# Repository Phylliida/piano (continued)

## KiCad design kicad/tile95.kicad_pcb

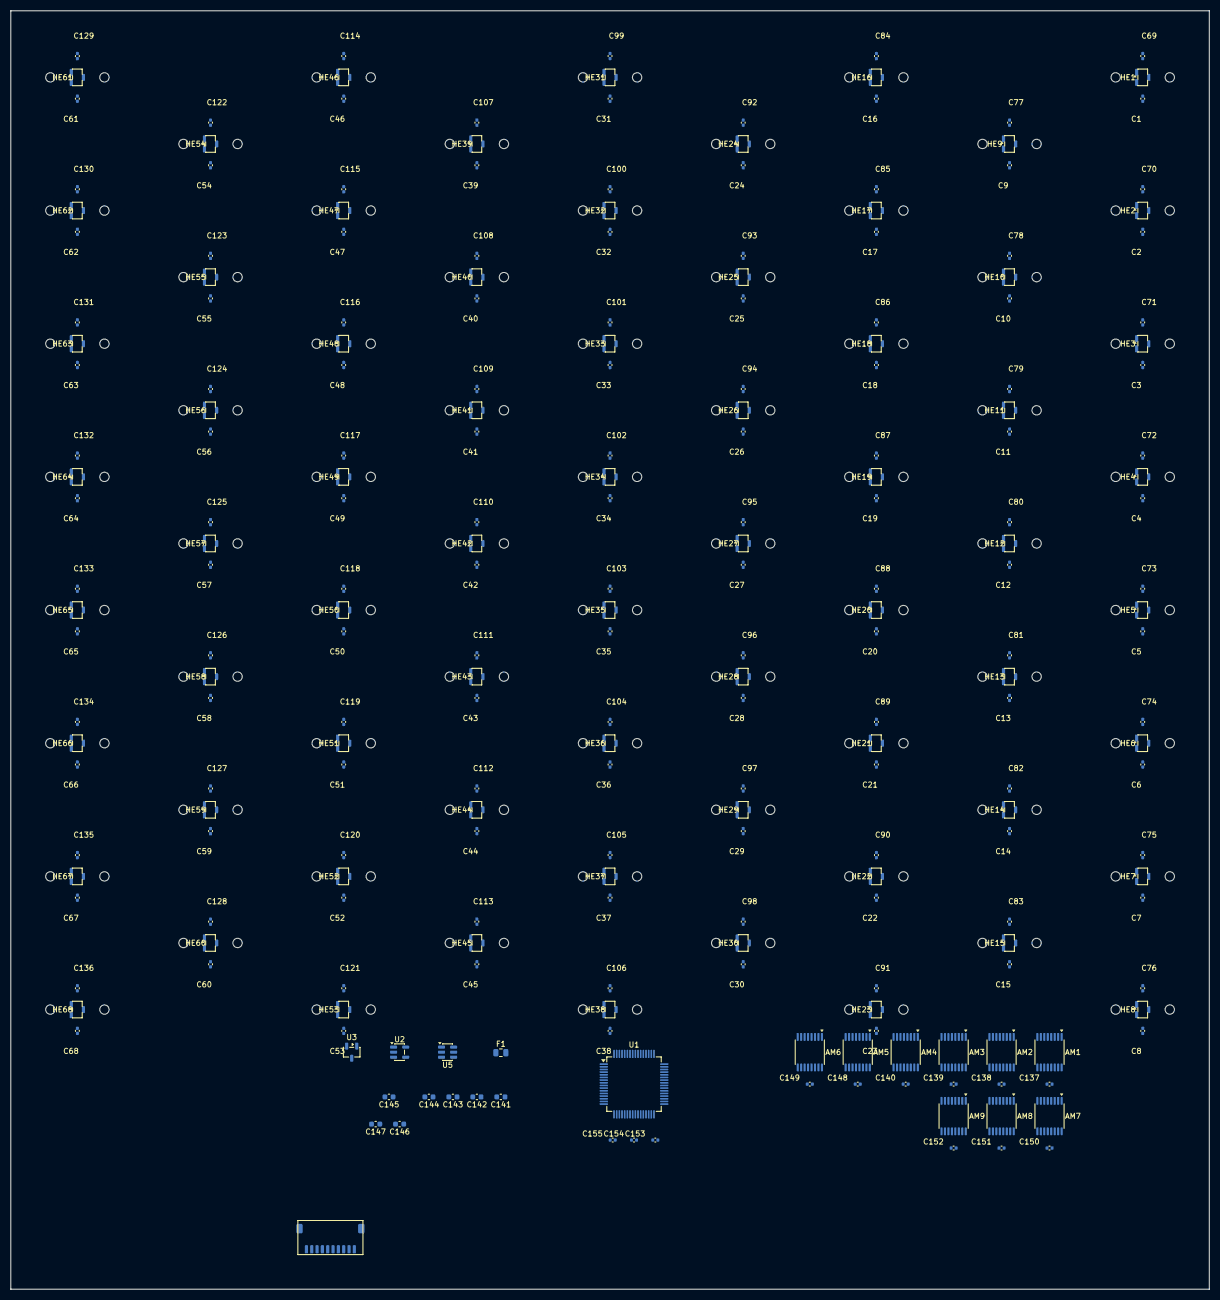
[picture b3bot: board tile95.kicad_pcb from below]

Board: 2 copper layers, 225.0 x 240.0 mm, 306 parts (238 on the bottom side), 89 nets, no tracks yet.

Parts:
AM1, AM2, AM3, AM4, AM5, AM6, AM7, AM8, AM9: SN74LV4051A; TSSOP-16_4.4x5mm_P0.65mm
C1, C2, C3, C4, C5, C6, C7, C8, C9, C10, C11, C12, C13, C14, C15, C16, C17, C18, C19, C20, C21, C22, C23, C24, C25, C26, C27, C28, C29, C30, C31, C32, C33, C34, C35, C36, C37, C38, C39, C40, C41, C42, C43, C44, C45, C46, C47, C48, C49, C50, C51, C52, C53, C54, C55, C56, C57, C58, C59, C60, C61, C62, C63, C64, C65, C66, C67, C68: 4.7n; C_0402_1005Metric
C69, C70, C71, C72, C73, C74, C75, C76, C77, C78, C79, C80, C81, C82, C83, C84, C85, C86, C87, C88, C89, C90, C91, C92, C93, C94, C95, C96, C97, C98, C99, C100, C101, C102, C103, C104, C105, C106, C107, C108, C109, C110, C111, C112, C113, C114, C115, C116, C117, C118, C119, C120, C121, C122, C123, C124, C125, C126, C127, C128, C129, C130, C131, C132, C133, C134, C135, C136, C137, C138, C139, C140, C148, C149, C150, C151, C152, C153, C154, C155: 100n; C_0402_1005Metric
C141, C142, C143, C144, C146: 2.2u; C_0603_1608Metric
C145: 10u; C_0603_1608Metric
C147: 1u; C_0603_1608Metric
F1: BSMD0805-050-24V; Fuse_0805_2012Metric
HE1, HE2, HE3, HE4, HE5, HE6, HE7, HE8, HE9, HE10, HE11, HE12, HE13, HE14, HE15, HE16, HE17, HE18, HE19, HE20, HE21, HE22, HE23, HE24, HE25, HE26, HE27, HE28, HE29, HE30, HE31, HE32, HE33, HE34, HE35, HE36, HE37, HE38, HE39, HE40, HE41, HE42, HE43, HE44, HE45, HE46, HE47, HE48, HE49, HE50, HE51, HE52, HE53, HE54, HE55, HE56, HE57, HE58, HE59, HE60, HE61, HE62, HE63, HE64, HE65, HE66, HE67, HE68: GH39FKSW; SOT-23-3
J1: SM10B-SRSS-TB; JST_SH_SM10B-SRSS-TB_1x10-1MP_P1.00mm_Horizontal
SW1, SW2, SW3, SW4, SW5, SW6, SW7, SW8, SW9, SW10, SW11, SW12, SW13, SW14, SW15, SW16, SW17, SW18, SW19, SW20, SW21, SW22, SW23, SW24, SW25, SW26, SW27, SW28, SW29, SW30, SW31, SW32, SW33, SW34, SW35, SW36, SW37, SW38, SW39, SW40, SW41, SW42, SW43, SW44, SW45, SW46, SW47, SW48, SW49, SW50, SW51, SW52, SW53, SW54, SW55, SW56, SW57, SW58, SW59, SW60, SW61, SW62, SW63, SW64, SW65, SW66, SW67, SW68: MX-1U
U1: AT32F405RCT7; LQFP-64_10x10mm_P0.5mm
U2: TLV75733PDBV; SOT-23-5
U3: XC6206P332MR-G; SOT-23-3
U5: USBLC6-2SC6; SOT-23-6

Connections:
5V: C141.1, C142.1, C143.1, C144.1, F1.2, U2.1 (IN), U2.3 (EN), U3.3 (GND), U5.5 (VBUS)
+3V3: C145.1, C153.1, C154.1, C155.1, U1.1 (VDD), U1.36 (VDD), U1.64 (VDD), U3.2 (OUT)
+3V3A: AM1.16 (VDD), AM2.16 (VDD), AM3.16 (VDD), AM4.16 (VDD), AM5.16 (VDD), AM6.16 (VDD), AM7.16 (VDD), AM8.16 (VDD), AM9.16 (VDD), C69.1, C70.1, C71.1, C72.1, C73.1, C74.1, C75.1, C76.1, C77.1, C78.1, C79.1, C80.1, C81.1, C82.1, C83.1, C84.1, C85.1, C86.1, C87.1, C88.1, C89.1, C90.1, C91.1, C92.1, C93.1, C94.1, C95.1, C96.1, C97.1, C98.1, C99.1, C100.1, C101.1, C102.1, C103.1, C104.1, C105.1, C106.1, C107.1, C108.1, C109.1, C110.1, C111.1, C112.1, C113.1, C114.1, C115.1, C116.1, C117.1, C118.1, C119.1, C120.1, C121.1, C122.1, C123.1, C124.1, C125.1, C126.1, C127.1, C128.1, C129.1, C130.1, C131.1, C132.1, C133.1, C134.1, C135.1, C136.1, C137.1, C138.1, C139.1, C140.1, C146.1, C147.1, C148.1, C149.1, C150.1, C151.1, C152.1, HE1.1 (VCC), HE2.1 (VCC), HE3.1 (VCC), HE4.1 (VCC), HE5.1 (VCC), HE6.1 (VCC), HE7.1 (VCC), HE8.1 (VCC), HE9.1 (VCC), HE10.1 (VCC), HE11.1 (VCC), HE12.1 (VCC), HE13.1 (VCC), HE14.1 (VCC), HE15.1 (VCC), HE16.1 (VCC), HE17.1 (VCC), HE18.1 (VCC), HE19.1 (VCC), HE20.1 (VCC), HE21.1 (VCC), HE22.1 (VCC), HE23.1 (VCC), HE24.1 (VCC), HE25.1 (VCC), HE26.1 (VCC), HE27.1 (VCC), HE28.1 (VCC), HE29.1 (VCC), HE30.1 (VCC), HE31.1 (VCC), HE32.1 (VCC), HE33.1 (VCC), HE34.1 (VCC), HE35.1 (VCC), HE36.1 (VCC), HE37.1 (VCC), HE38.1 (VCC), HE39.1 (VCC), HE40.1 (VCC), HE41.1 (VCC), HE42.1 (VCC), HE43.1 (VCC), HE44.1 (VCC), HE45.1 (VCC), HE46.1 (VCC), HE47.1 (VCC), HE48.1 (VCC), HE49.1 (VCC), HE50.1 (VCC), HE51.1 (VCC), HE52.1 (VCC), HE53.1 (VCC), HE54.1 (VCC), HE55.1 (VCC), HE56.1 (VCC), HE57.1 (VCC), HE58.1 (VCC), HE59.1 (VCC), HE60.1 (VCC), HE61.1 (VCC), HE62.1 (VCC), HE63.1 (VCC), HE64.1 (VCC), HE65.1 (VCC), HE66.1 (VCC), HE67.1 (VCC), HE68.1 (VCC), U1.13 (VDDA), U2.5 (OUT)
GND: AM1.6 (Inh), AM1.7 (VEE), AM1.8 (VSS), AM2.6 (Inh), AM2.7 (VEE), AM2.8 (VSS), AM3.6 (Inh), AM3.7 (VEE), AM3.8 (VSS), AM4.6 (Inh), AM4.7 (VEE), AM4.8 (VSS), AM5.6 (Inh), AM5.7 (VEE), AM5.8 (VSS), AM6.6 (Inh), AM6.7 (VEE), AM6.8 (VSS), AM7.6 (Inh), AM7.7 (VEE), AM7.8 (VSS), AM8.6 (Inh), AM8.7 (VEE), AM8.8 (VSS), AM9.6 (Inh), AM9.7 (VEE), AM9.8 (VSS), AM9.12 (X3), AM9.13 (X0), AM9.14 (X1), AM9.15 (X2), C1.2, C2.2, C3.2, C4.2, C5.2, C6.2, C7.2, C8.2, C9.2, C10.2, C11.2, C12.2, C13.2, C14.2, C15.2, C16.2, C17.2, C18.2, C19.2, C20.2, C21.2, C22.2, C23.2, C24.2, C25.2, C26.2, C27.2, C28.2, C29.2, C30.2, C31.2, C32.2, C33.2, C34.2, C35.2, C36.2, C37.2, C38.2, C39.2, C40.2, C41.2, C42.2, C43.2, C44.2, C45.2, C46.2, C47.2, C48.2, C49.2, C50.2, C51.2, C52.2, C53.2, C54.2, C55.2, C56.2, C57.2, C58.2, C59.2, C60.2, C61.2, C62.2, C63.2, C64.2, C65.2, C66.2, C67.2, C68.2, C69.2, C70.2, C71.2, C72.2, C73.2, C74.2, C75.2, C76.2, C77.2, C78.2, C79.2, C80.2, C81.2, C82.2, C83.2, C84.2, C85.2, C86.2, C87.2, C88.2, C89.2, C90.2, C91.2, C92.2, C93.2, C94.2, C95.2, C96.2, C97.2, C98.2, C99.2, C100.2, C101.2, C102.2, C103.2, C104.2, C105.2, C106.2, C107.2, C108.2, C109.2, C110.2, C111.2, C112.2, C113.2, C114.2, C115.2, C116.2, C117.2, C118.2, C119.2, C120.2, C121.2, C122.2, C123.2, C124.2, C125.2, C126.2, C127.2, C128.2, C129.2, C130.2, C131.2, C132.2, C133.2, C134.2, C135.2, C136.2, C137.2, C138.2, C139.2, C140.2, C141.2, C142.2, C143.2, C144.2, C145.2, C146.2, C147.2, C148.2, C149.2, C150.2, C151.2, C152.2, C153.2, C154.2, C155.2, HE1.3 (GND), HE2.3 (GND), HE3.3 (GND), HE4.3 (GND), HE5.3 (GND), HE6.3 (GND), HE7.3 (GND), HE8.3 (GND), HE9.3 (GND), HE10.3 (GND), HE11.3 (GND), HE12.3 (GND), HE13.3 (GND), HE14.3 (GND), HE15.3 (GND), HE16.3 (GND), HE17.3 (GND), HE18.3 (GND), HE19.3 (GND), HE20.3 (GND), HE21.3 (GND), HE22.3 (GND), HE23.3 (GND), HE24.3 (GND), HE25.3 (GND), HE26.3 (GND), HE27.3 (GND), HE28.3 (GND), HE29.3 (GND), HE30.3 (GND), HE31.3 (GND), HE32.3 (GND), HE33.3 (GND), HE34.3 (GND), HE35.3 (GND), HE36.3 (GND), HE37.3 (GND), HE38.3 (GND), HE39.3 (GND), HE40.3 (GND), HE41.3 (GND), HE42.3 (GND), HE43.3 (GND), HE44.3 (GND), HE45.3 (GND), HE46.3 (GND), HE47.3 (GND), HE48.3 (GND), HE49.3 (GND), HE50.3 (GND), HE51.3 (GND), HE52.3 (GND), HE53.3 (GND), HE54.3 (GND), HE55.3 (GND), HE56.3 (GND), HE57.3 (GND), HE58.3 (GND), HE59.3 (GND), HE60.3 (GND), HE61.3 (GND), HE62.3 (GND), HE63.3 (GND), HE64.3 (GND), HE65.3 (GND), HE66.3 (GND), HE67.3 (GND), HE68.3 (GND), J1.3, J1.4, J1.7, J1.8, U1.12 (VSSA), U1.31 (VSS), U1.63 (VSS), U2.2 (GND), U3.1 (VCC), U5.2 (GND)
HE1: AM1.1 (X4), C1.1, HE1.2 (OUT)
HE2: AM1.2 (X6), C2.1, HE2.2 (OUT)
HE3: AM1.4 (X7), C3.1, HE3.2 (OUT)
HE4: AM1.5 (X5), C4.1, HE4.2 (OUT)
HE5: AM1.15 (X2), C5.1, HE5.2 (OUT)
HE6: AM1.14 (X1), C6.1, HE6.2 (OUT)
HE7: AM1.13 (X0), C7.1, HE7.2 (OUT)
HE8: AM1.12 (X3), C8.1, HE8.2 (OUT)
HE9: AM2.1 (X4), C9.1, HE9.2 (OUT)
HE10: AM2.2 (X6), C10.1, HE10.2 (OUT)
HE11: AM2.4 (X7), C11.1, HE11.2 (OUT)
HE12: AM2.5 (X5), C12.1, HE12.2 (OUT)
HE13: AM2.15 (X2), C13.1, HE13.2 (OUT)
HE14: AM2.14 (X1), C14.1, HE14.2 (OUT)
HE15: AM2.13 (X0), C15.1, HE15.2 (OUT)
HE16: AM2.12 (X3), C16.1, HE16.2 (OUT)
HE17: AM3.1 (X4), C17.1, HE17.2 (OUT)
HE18: AM3.2 (X6), C18.1, HE18.2 (OUT)
HE19: AM3.4 (X7), C19.1, HE19.2 (OUT)
HE20: AM3.5 (X5), C20.1, HE20.2 (OUT)
HE21: AM3.15 (X2), C21.1, HE21.2 (OUT)
HE22: AM3.14 (X1), C22.1, HE22.2 (OUT)
HE23: AM3.13 (X0), C23.1, HE23.2 (OUT)
HE24: AM3.12 (X3), C24.1, HE24.2 (OUT)
HE25: AM4.1 (X4), C25.1, HE25.2 (OUT)
HE26: AM4.2 (X6), C26.1, HE26.2 (OUT)
HE27: AM4.4 (X7), C27.1, HE27.2 (OUT)
HE28: AM4.5 (X5), C28.1, HE28.2 (OUT)
HE29: AM4.15 (X2), C29.1, HE29.2 (OUT)
HE30: AM4.14 (X1), C30.1, HE30.2 (OUT)
HE31: AM4.13 (X0), C31.1, HE31.2 (OUT)
HE32: AM4.12 (X3), C32.1, HE32.2 (OUT)
HE33: AM5.1 (X4), C33.1, HE33.2 (OUT)
HE34: AM5.2 (X6), C34.1, HE34.2 (OUT)
HE35: AM5.4 (X7), C35.1, HE35.2 (OUT)
HE36: AM5.5 (X5), C36.1, HE36.2 (OUT)
HE37: AM5.15 (X2), C37.1, HE37.2 (OUT)
HE38: AM5.14 (X1), C38.1, HE38.2 (OUT)
HE39: AM5.13 (X0), C39.1, HE39.2 (OUT)
HE40: AM5.12 (X3), C40.1, HE40.2 (OUT)
HE41: AM6.1 (X4), C41.1, HE41.2 (OUT)
HE42: AM6.2 (X6), C42.1, HE42.2 (OUT)
HE43: AM6.4 (X7), C43.1, HE43.2 (OUT)
HE44: AM6.5 (X5), C44.1, HE44.2 (OUT)
HE45: AM6.15 (X2), C45.1, HE45.2 (OUT)
HE46: AM6.14 (X1), C46.1, HE46.2 (OUT)
HE47: AM6.13 (X0), C47.1, HE47.2 (OUT)
HE48: AM6.12 (X3), C48.1, HE48.2 (OUT)
HE49: AM7.1 (X4), C49.1, HE49.2 (OUT)
HE50: AM7.2 (X6), C50.1, HE50.2 (OUT)
HE51: AM7.4 (X7), C51.1, HE51.2 (OUT)
HE52: AM7.5 (X5), C52.1, HE52.2 (OUT)
HE53: AM7.15 (X2), C53.1, HE53.2 (OUT)
HE54: AM7.14 (X1), C54.1, HE54.2 (OUT)
HE55: AM7.13 (X0), C55.1, HE55.2 (OUT)
HE56: AM7.12 (X3), C56.1, HE56.2 (OUT)
HE57: AM8.1 (X4), C57.1, HE57.2 (OUT)
HE58: AM8.2 (X6), C58.1, HE58.2 (OUT)
HE59: AM8.4 (X7), C59.1, HE59.2 (OUT)
HE60: AM8.5 (X5), C60.1, HE60.2 (OUT)
HE61: AM8.15 (X2), C61.1, HE61.2 (OUT)
HE62: AM8.14 (X1), C62.1, HE62.2 (OUT)
HE63: AM8.13 (X0), C63.1, HE63.2 (OUT)
HE64: AM8.12 (X3), C64.1, HE64.2 (OUT)
HE65: AM9.1 (X4), C65.1, HE65.2 (OUT)
HE66: AM9.2 (X6), C66.1, HE66.2 (OUT)
HE67: AM9.4 (X7), C67.1, HE67.2 (OUT)
HE68: AM9.5 (X5), C68.1, HE68.2 (OUT)
MUX_OUT_1: AM1.3 (X), U1.17 (PA3)
MUX_OUT_2: AM2.3 (X), U1.20 (PA4)
MUX_OUT_3: AM3.3 (X), U1.21 (PA5)
MUX_OUT_4: AM4.3 (X), U1.22 (PA6)
MUX_OUT_5: AM5.3 (X), U1.23 (PA7)
MUX_OUT_6: AM6.3 (X), U1.24 (PC4)
MUX_OUT_7: AM7.3 (X), U1.25 (PC5)
MUX_OUT_8: AM8.3 (X), U1.26 (PB0)
MUX_OUT_9: AM9.3 (X), U1.27 (PB1)
MUX_SELECT_0: AM1.11 (A), AM2.11 (A), AM3.11 (A), AM4.11 (A), AM5.11 (A), AM6.11 (A), AM7.11 (A), AM8.11 (A), AM9.11 (A), U1.9 (PC1)
MUX_SELECT_1: AM1.10 (B), AM2.10 (B), AM3.10 (B), AM4.10 (B), AM5.10 (B), AM6.10 (B), AM7.10 (B), AM8.10 (B), AM9.10 (B), U1.10 (PC2)
MUX_SELECT_2: AM1.9 (C), AM2.9 (C), AM3.9 (C), AM4.9 (C), AM5.9 (C), AM6.9 (C), AM7.9 (C), AM8.9 (C), AM9.9 (C), U1.11 (PC3)
USB_D+: U1.35 (OTGHS1_D+), U5.4 (I/O2)
USB_D-: U1.34 (OTGHS1_D-), U5.3 (I/O2)
USB_PLUG_D+: J1.5, U5.6 (I/O1)
USB_PLUG_D-: J1.6, U5.1 (I/O1)
VBUS: F1.1, J1.1, J1.2

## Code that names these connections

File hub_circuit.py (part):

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# Every MCU signal: net -> (pin number, pin name).  firmware/hub/board.h is a
# copy of this table.
PINS = {
    "USB_DM": ("44", "PA11"), "USB_DP": ("45", "PA12"),          # OTGFS1, also the ROM's USB DFU
    "LINK_TX": ("16", "PA2"), "LINK_RX": ("17", "PA3"),          # USART2
    "AUX_TX": ("51", "PC10"), "AUX_RX": ("52", "PC11"),          # USART3, a ROM bootloader UART
    "PD_SCL": ("58", "PB6"), "PD_SDA": ("59", "PB7"),            # I2C1 to the CH224A
    "PD_PG": ("57", "PB5"),                                      # low = the charger agreed
    "EN_PD": ("30", "PB12"), "EN_HOST": ("32", "PB13"),          # high = eFuse on
    "ILIM_HI": ("28", "PB2"),                                    # open drain; low = 1.43 A from USB
    "FLT_PD": ("61", "PB8"), "FLT_HOST": ("62", "PB9"),          # low = fault
    "VIN_SENSE": ("8", "PC0"), "VPD_SENSE": ("9", "PC1"),        # ADC1_IN10, IN11
    "VBUS_SENSE": ("10", "PC2"), "IMON_PD": ("11", "PC3"),       # ADC1_IN12, IN13
    "IMON_HOST": ("14", "PA0"),                                  # ADC1_IN0
    "CC1_SENSE": ("15", "PA1"), "CC2_SENSE": ("20", "PA4"),      # ADC1_IN1, IN4
    "LED_STATUS": ("37", "PC6"), "LED_POWER": ("38", "PC7"),     # high = lit
    "BTN_USER": ("2", "PC13"),                                   # low = pressed
    "SWDIO": ("46", "PA13"), "SWCLK": ("49", "PA14"),
    "BOOT0": ("60", "PF11/BOOT0"),
}
# What the ADC sees, for the firmware.
VIN_DIVIDER = (100e3, 15e3)         # VIN and V_PD: top, bottom
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connect("+3V3", (U1.ref, 1, "VDD"), (U1.ref, 36, "VDD"), (U1.ref, 64, "VDD"))
connect("GND", (U1.ref, 31, "VSS"), (U1.ref, 63, "VSS"), (U1.ref, 12, "VSSA"))
connect("+3.3VA", (U1.ref, 13, "VDDA"))
connect("HEXT_IN", (U1.ref, 5, "PF0/HEXT_IN"))
connect("HEXT_OUT", (U1.ref, 6, "PF1/HEXT_OUT"))
connect("NRST", (U1.ref, 7, "NRST"))
connect("OTGHS_R", (U1.ref, 33, "OTGHS1_R"))     # DS Table 9 note 5: 12k 1% to GND
for net, pin in PINS.items():
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    connect("GND", (J_PWR.ref, pin, "GND"))
connect("GND", (J_PWR.ref, "S1", "SHIELD"))
for pin in ("A4", "A9", "B4", "B9"):
    connect("V_PD", (J_PWR.ref, pin, "VBUS"))
connect("PD_CC1", (J_PWR.ref, "A5", "CC1"))
connect("PD_CC2", (J_PWR.ref, "B5", "CC2"))
connect("PD_DP", (J_PWR.ref, "A6", "D+"), (J_PWR.ref, "B6", "D+"))
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# log, and the ROM bootloader, which listens on this UART too.
AUX = part("J", "Connector_Generic:Conn_01x03", "AUX",
           "Connector_PinHeader_2.54mm:PinHeader_1x03_P2.54mm_Vertical_SMD_Pin1Left", "link", dnp=True)
for pin, net in enumerate(["GND", "AUX_TX", "AUX_RX"], 1):
    connect(net, (AUX.ref, pin))

# ----------------------------------------------------------------------- ui ---
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
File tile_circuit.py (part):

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# one regulator; VDDA and the sensors take it through a ferrite (see power).
# The sensors share VDDA, so readings stay ratiometric, as on HE60.
connect("+3.3VA", (U1.ref, 13, "VDDA"))
connect("HEXT_IN", (U1.ref, 5, "PF0/HEXT_IN"))
connect("HEXT_OUT", (U1.ref, 6, "PF1/HEXT_OUT"))
connect("NRST", (U1.ref, 7, "NRST"))
connect("OTGHS_R", (U1.ref, 33, "OTGHS1_R"))     # DS Table 9 note 5: 12k 1% to GND
# Signal pins are picked for the copper (route_board.py), among the pins that
# can do the job (DS Table 9).  The three selects and MUX_OUT4 leave U1's top
# side side by side, straight into AM4 next to it; the other four mux outputs
# come up the middle of the board on the front and drop onto PA4-PA7 under U1.
SELECT_PINS = [("26", "PB0"), ("25", "PC5"), ("24", "PC4")]         # MUX_S0, S1, S2
for i, pin in enumerate(SELECT_PINS):
    connect("MUX_S%d" % i, (U1.ref,) + pin)
# MUX_OUT1..5 -> ADC1_IN4, IN5, IN6, IN9, IN7 (IN0-7 = PA0-7, IN8/9 = PB0/1, IN10-15 = PC0-5)
ADC_PINS = [("20", "PA4"), ("21", "PA5"), ("22", "PA6"), ("27", "PB1"), ("23", "PA7")]
ADC_CHANNEL = [4, 5, 6, 9, 7]
for m in range(g.ROWS):
    connect("MUX_OUT%d" % (m + 1), (U1.ref,) + ADC_PINS[m])
# One UART per edge, (TX, RX), each on the side of U1 its port is on.  W and S
# are also UARTs the ROM bootloader listens on (DS Table 5: USART2 PA2/PA3,
# USART3 PC10/PC11).  The IOMUX number of each pin is in RM chapter 6.
UARTS = {"W": (("16", "PA2"), ("17", "PA3")),       # USART2
         "N": (("37", "PC6"), ("38", "PC7")),       # USART6
         "E": (("39", "PC8"), ("40", "PC9")),       # UART8
         "S": (("51", "PC10"), ("52", "PC11"))}     # USART3
for edge, (tx, rx) in UARTS.items():
    connect("%s_TX" % edge, (U1.ref,) + tx)
    connect("%s_RX" % edge, (U1.ref,) + rx)
connect("SWDIO", (U1.ref, 46, "PA13"))
connect("SWCLK", (U1.ref, 49, "PA14"))
connect("BOOT0", (U1.ref, 60, "PF11/BOOT0"))
connect("PA11_PD", (U1.ref, 44, "PA11"))
connect("PA12_PD", (U1.ref, 45, "PA12"))
for _ in range(3):
    cap("100n/16V", "+3V3", "GND", "mcu")            # one per VDD pin
cap("4.7u/10V", "+3V3", "GND", "mcu", footprint=FP_C0603)
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cap("1u/16V", "+3.3VA", "GND", "mcu")
cap("100n/16V", "NRST", "GND", "mcu")                # DS Fig. 19
res("3.3k", "BOOT0", "GND", "mcu")                   # DS: pull-down <= 3.3k
res("100k", "PA11_PD", "GND", "mcu")                 # errata ES0011 1.5.2: PA11/12
res("100k", "PA12_PD", "GND", "mcu")                 # float high otherwise
res("12k 1%", "OTGHS_R", "GND", "mcu")               # USB PHY bias, even unused
Y1 = part("Y", "Device:Crystal_GND24", "12MHz", "Crystal:Crystal_SMD_3225-4Pin_3.2x2.5mm", "mcu",
          mpn="X322512MSB4SI")
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
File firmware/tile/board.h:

/* The tile board's wiring, as the firmware needs it: a copy of the tables
 * in tile_circuit.py (SELECT_PINS, ADC_PINS, ADC_CHANNEL, CHANNEL_OF_COL,
 * UARTS). If that file changes, this one has to follow. */
#ifndef PIANO_TILE_BOARD_H
#define PIANO_TILE_BOARD_H

#include "port.h"

/* SELECT_PINS: the three select lines every mux shares.
 * MUX_S0 = PB0, MUX_S1 = PC5, MUX_S2 = PC4. */
#define SEL0_GPIO   GPIOB
#define SEL0_PIN    GPIO_PINS_0
#define SEL1_GPIO   GPIOC
#define SEL1_PIN    GPIO_PINS_5
#define SEL2_GPIO   GPIOC
#define SEL2_PIN    GPIO_PINS_4

/* ADC_PINS and ADC_CHANNEL: mux m reads key row m, and its output
 * MUX_OUT1..5 is on PA4, PA5, PA6, PB1, PA7 = ADC1_IN4, IN5, IN6, IN9, IN7. */
#define ADC_GPIOA_PINS  (GPIO_PINS_4 | GPIO_PINS_5 | GPIO_PINS_6 | GPIO_PINS_7)
#define ADC_GPIOB_PINS  GPIO_PINS_1
#define ADC_CHANNEL_OF_ROW \
    { ADC_CHANNEL_4, ADC_CHANNEL_5, ADC_CHANNEL_6, ADC_CHANNEL_9, ADC_CHANNEL_7 }

/* CHANNEL_OF_COL[row][column]: the key in (column c, row m) is read at
 * select value CHANNEL_OF_COL[m][c]. Row 3's mux is turned a quarter turn
 * on the board and has an order of its own. */
#define CHANNEL_OF_COL \
    { { 6, 7, 4, 5, 2, 3, 1, 0 }, \
      { 6, 7, 4, 5, 2, 3, 1, 0 }, \
      { 6, 7, 4, 5, 2, 3, 1, 0 }, \
      { 0, 1, 3, 2, 5, 4, 7, 6 }, \
      { 6, 7, 4, 5, 2, 3, 1, 0 } }

/* UARTS: one per edge, (TX, RX) = the cable's pins (A, B) through 220 ohm.
 *   W  USART2  PA2,  PA3     (also a ROM bootloader UART)
 *   N  USART6  PC6,  PC7
 *   E  UART8   PC8,  PC9
 *   S  USART3  PC10, PC11    (also a ROM bootloader UART)
 * The IOMUX numbers are from the reference manual's chapter 6; the DMA
 * channels are ours to choose (any request can go to any channel). */
#define UART_W_HW { \
    USART2, CRM_USART2_PERIPH_CLOCK, GPIOA, GPIO_PINS_2, GPIO_PINS_3, \
    GPIO_PINS_SOURCE2, GPIO_PINS_SOURCE3, GPIO_MUX_7, \
    DMA1, DMA1_CHANNEL2, DMA1_CHANNEL3, DMA1MUX_CHANNEL2, DMA1MUX_CHANNEL3, \
    DMAMUX_DMAREQ_ID_USART2_RX, DMAMUX_DMAREQ_ID_USART2_TX }
#define UART_N_HW { \
    USART6, CRM_USART6_PERIPH_CLOCK, GPIOC, GPIO_PINS_6, GPIO_PINS_7, \
    GPIO_PINS_SOURCE6, GPIO_PINS_SOURCE7, GPIO_MUX_8, \
    DMA1, DMA1_CHANNEL4, DMA1_CHANNEL5, DMA1MUX_CHANNEL4, DMA1MUX_CHANNEL5, \
    DMAMUX_DMAREQ_ID_USART6_RX, DMAMUX_DMAREQ_ID_USART6_TX }
#define UART_E_HW { \
    UART8, CRM_UART8_PERIPH_CLOCK, GPIOC, GPIO_PINS_8, GPIO_PINS_9, \
    GPIO_PINS_SOURCE8, GPIO_PINS_SOURCE9, GPIO_MUX_7, \
    DMA1, DMA1_CHANNEL6, DMA1_CHANNEL7, DMA1MUX_CHANNEL6, DMA1MUX_CHANNEL7, \
    DMAMUX_DMAREQ_ID_UART8_RX, DMAMUX_DMAREQ_ID_UART8_TX }
#define UART_S_HW { \
    USART3, CRM_USART3_PERIPH_CLOCK, GPIOC, GPIO_PINS_10, GPIO_PINS_11, \
    GPIO_PINS_SOURCE10, GPIO_PINS_SOURCE11, GPIO_MUX_7, \
    DMA2, DMA2_CHANNEL1, DMA2_CHANNEL2, DMA2MUX_CHANNEL1, DMA2MUX_CHANNEL2, \
    DMAMUX_DMAREQ_ID_USART3_RX, DMAMUX_DMAREQ_ID_USART3_TX }

#endif

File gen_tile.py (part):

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# ------------------------------------------------------------------- netlist ---
# ADC pins verified from the HE60 netlist: its 9 mux outputs land on these.
ADC_PINS = ["17", "20", "21", "22", "23", "24", "25", "26", "27", "14", "15", "16"]
# 17=PA3 20=PA4 21=PA5 22=PA6 23=PA7 24=PC4 25=PC5 26=PB0 27=PB1 14=PA0 15=PA1 16=PA2
MUX_SELECT_PINS = ["9", "10", "11"]        # PC1 / PC2 / PC3 (verified against the
                                           # AT32F405 footprint pinfunctions; HE60
                                           # and he60-v2 use C1/C2/C3 too)
USB_PINS = {"34": "USB_D-", "35": "USB_D+"}
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    put("U1", "13", "+3V3A")
    for i in range(n_mux):
        put("U1", ADC_PINS[i], f"MUX_OUT_{i + 1}")
    for pin, nm in zip(MUX_SELECT_PINS, ("MUX_SELECT_0", "MUX_SELECT_1", "MUX_SELECT_2")):
        put("U1", pin, nm)
    put("U1", "34", "USB_D-"); put("U1", "35", "USB_D+"); put("U1", "7", "NRST")
    for pin, nm in CONN_PINS.items():
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    put("U1", "13", "+3V3A")
    for i in range(n_mux):
        put("U1", ADC_PINS[i], f"MUX_OUT_{i + 1}")
    for pin, nm in zip(MUX_SELECT_PINS, ("MUX_SELECT_0", "MUX_SELECT_1", "MUX_SELECT_2")):
        put("U1", pin, nm)
    put("U1", "34", "USB_D-"); put("U1", "35", "USB_D+"); put("U1", "7", "NRST")
    for pin, nm in CONN_PINS.items():
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    add_net("+3V3A", "U1", "13")
    for i in range(n_mux):
        add_net(f"MUX_OUT_{i + 1}", "U1", ADC_PINS[i])
    for pin, netname in zip(MUX_SELECT_PINS, ("MUX_SELECT_0", "MUX_SELECT_1", "MUX_SELECT_2")):
        add_net(netname, "U1", pin)
    add_net("USB_D-", "U1", "34")
    add_net("USB_D+", "U1", "35")
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
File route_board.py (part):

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# The front carries the mux lines up the middle of the board, between the pegs
# of columns 3 and 4.  x of each line where it runs straight:
BUS_X = {"MUX_OUT1": 90.6, "MUX_OUT2": 91.4, "MUX_OUT3": 92.2, "MUX_S2": 93.7, "MUX_S1": 94.5, "MUX_S0": 95.3}
SELECTS = [("MUX_S2", 9, 24), ("MUX_S1", 10, 25), ("MUX_S0", 11, 26)]     # net, mux pin, U1 pin; west to east
AM4_VIA_Y = {"MUX_S2": 48.0, "MUX_S1": 47.2, "MUX_S0": 48.0}  # AM4's select vias, north of its pins
OUT_VIA_X = 85.6                                # under U1: where the outputs come down from the front
OUT_VIA_Y = {5: 57.1, 3: 57.85, 2: 58.6, 1: 59.35}


def bus(r):
    """The three selects and the five mux outputs.  U1 hands the selects and
    MUX_OUT4 to AM4 beside it on the back; AM4's select pins pass them on to
    the front, which carries them north to AM5 and south to AM3, AM2, AM1.
    The other four outputs come to U1 on the front and drop onto its pins
    through vias under its body."""
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            px, py = r.pad("AM%d" % (m + 1), mpin)
            r.via(net, X, py)
            r.line(net, [(X, py), (px, py)])
    # MUX_OUT4: straight across, into AM4's pin 3 from between its rows
    ux, uy = r.pad("U1", 27)
    ax, ay = r.pad("AM4", 3)
    r.line("MUX_OUT4", [(ux, uy), (ux, 53.75 + c), (ux + c, 53.75), (ax - c, 53.75), (ax, 53.75 + c), (ax, ay)])
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    x, y = r.pad(series("S_TX")[0], 1)
    vx = 105.5
    r.line("S_TX", [(101.4, 70.0), (101.4, y - (vx - 101.4)), (vx, y)], "F")
    ax, ay = r.pad(tc.PORT["S"], pin_of(tc.PORT["S"], "S_A"))
    x2, y2 = r.pad(series("S_TX")[0], series("S_TX")[2])
    port("S", "TX", *via("S_TX", vx, y),
         bend=[(x2 - 0.6, y2 + 0.6), (ax + c, y2 + 0.6), (ax, y2 + 0.6 + c)])
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    via("S_RX", 100.6, 70.75)
    x, y = r.pad(series("S_RX")[0], 1)
    r.line("S_RX", [(100.6, 70.75), (100.6, y)], "F")
    bx, by = r.pad(tc.PORT["S"], pin_of(tc.PORT["S"], "S_B"))
    x2, y2 = r.pad(series("S_RX")[0], series("S_RX")[2])
    port("S", "RX", *via("S_RX", 100.6, y),
         bend=[(x2 + 0.5, y2 + 0.5), (bx - c, y2 + 0.5), (bx, y2 + 0.5 + c)])
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    P = "+3V3"
    # pull-downs beside their pins
    r.line("OTGHS_R", [("U1", 33), ("R4", 1)])
    r.line("PA11_PD", [("U1", 44), ("R2", 1)])
    (x, y), (rx, ry) = r.pad("U1", 45), r.pad("R3", 1)
    r.line("PA12_PD", [(x, y), (rx - (ry - y), y), (rx, ry)])
    # the debug pads, in the order the tracks leave U1: SWDIO, NRST, SWCLK, BOOT0 from north to south
    r.line("SWDIO", [("U1", 46), (89.7, 63.35), (90.0, 63.65), (90.0, 64.3), (90.4, 64.7), (92.5, 64.7),
                     (93.16, 64.04), ("J1", 5)])
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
